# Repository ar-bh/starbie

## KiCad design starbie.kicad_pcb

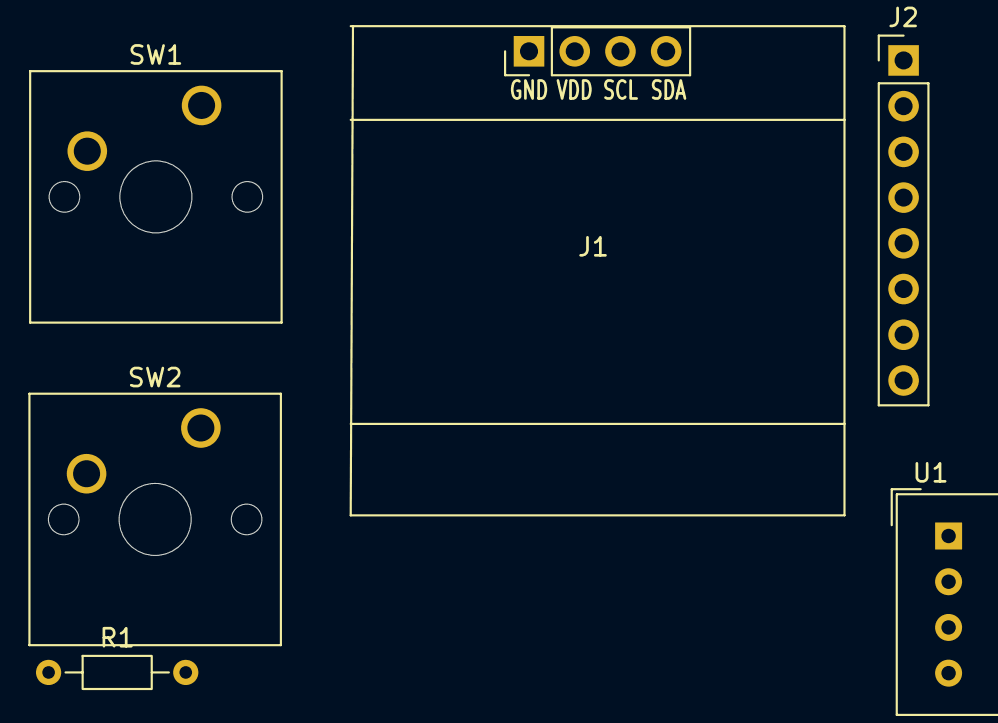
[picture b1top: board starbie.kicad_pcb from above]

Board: 2 copper layers, 6 parts (0 on the bottom side), 5 nets, no tracks yet.

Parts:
J1: Conn_01x04_Pin; Display_128x64_096_I2C
J2: Conn_01x08_Pin; PinHeader_1x08_P2.54mm_Vertical
R1: 10k; R_Axial_DIN0204_L3.6mm_D1.6mm_P7.62mm_Horizontal
SW1, SW2: SW_Push; SW_Cherry_MX_1.00u_PCB
U1: DHT11; Aosong_DHT11_5.5x12.0_P2.54mm

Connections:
+3.3V: J1.2, R1.1, U1.1 (VDD)
/DHT11 DATA: R1.2, U1.2 (DATA)
/SCL: J1.3, J2.3
/SDA: J1.4, J2.4
GND: J1.1, J2.2, SW1.2, SW2.2, U1.4 (GND)
